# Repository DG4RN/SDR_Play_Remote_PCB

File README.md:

# SDR_Play_Remote_PCB
PCB design (by KiCad) for remote switched antenna input in connection with raspberry pi.

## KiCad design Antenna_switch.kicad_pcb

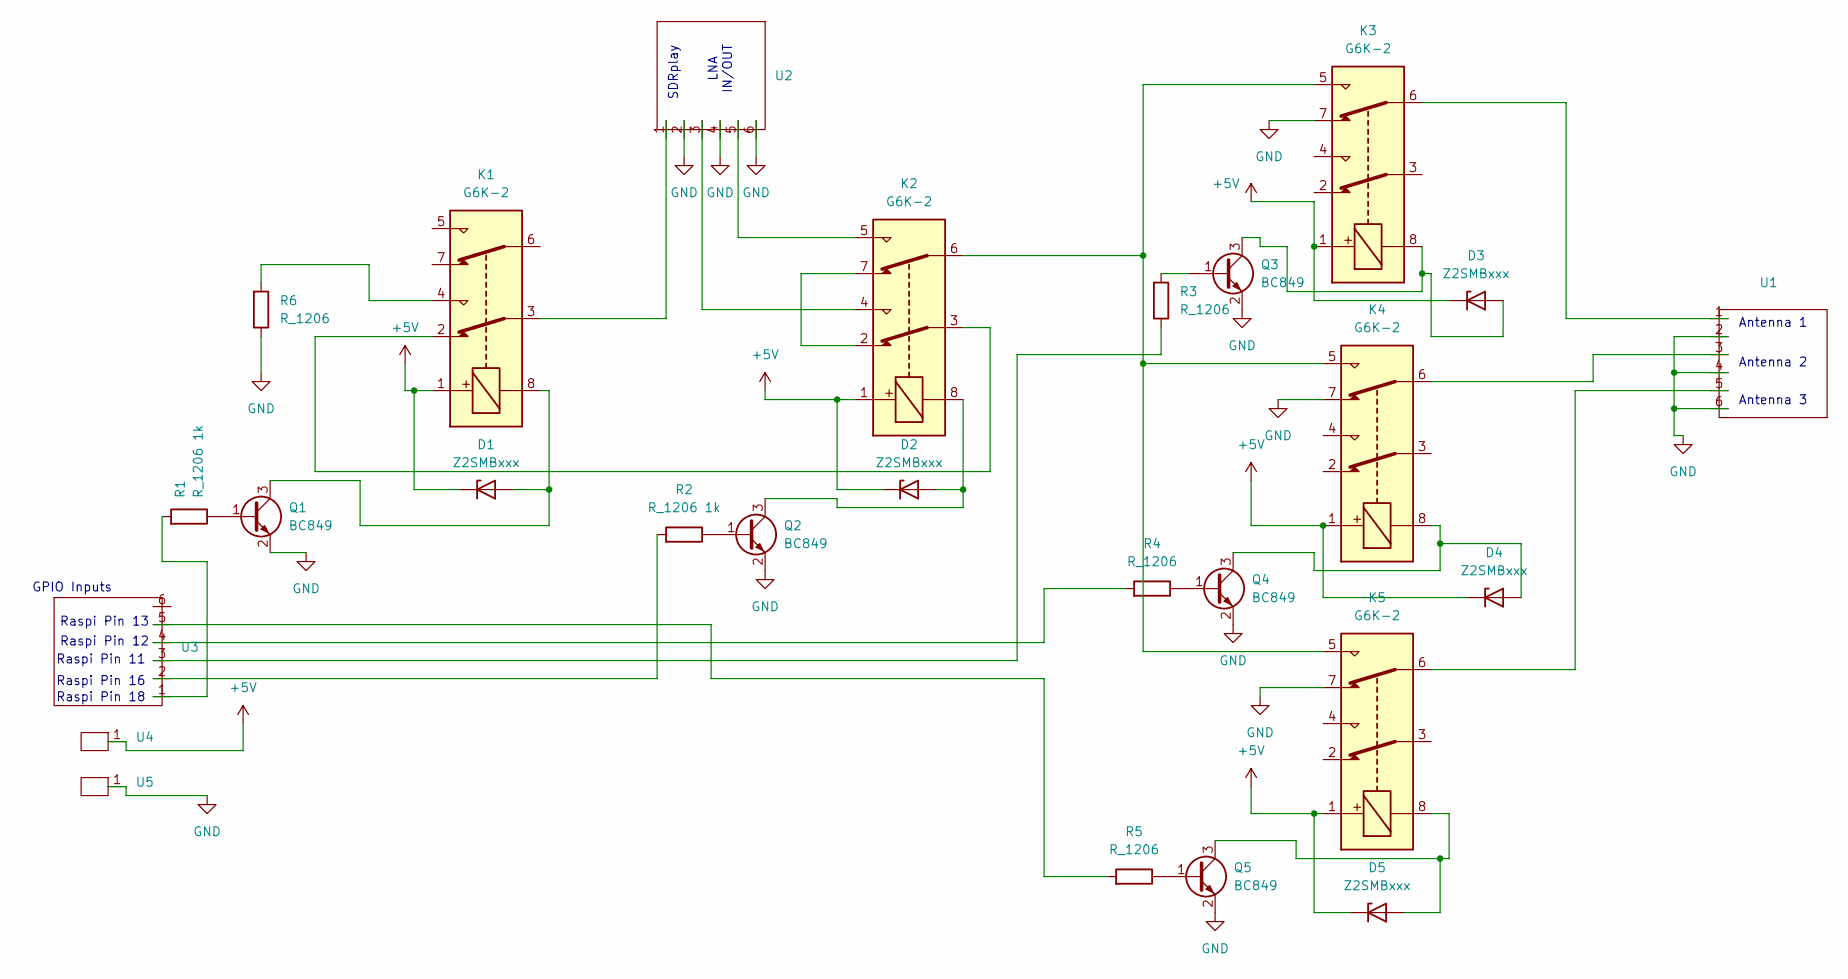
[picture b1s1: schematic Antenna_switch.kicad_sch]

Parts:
D1, D2, D3, D4, D5: Z2SMBxxx; D_SMB
K1, K2, K3, K4, K5: G6K-2; Relay_DPDT_Omron_G6K-2F-Y
Q1, Q2, Q3, Q4, Q5: BC849; SOT-23
R1, R2: R_1206 1k; R_1206_3216Metric
R3, R4, R5, R6: R_1206; R_1206_3216Metric
U1, U2, U3: Pad_IP-6
U4, U5: Lötpad_5_5

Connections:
+5V: D1.1 (K), D2.1 (K), D3.1 (K), D4.1 (K), D5.1 (K), K1.1, K2.1, K3.1, K4.1, K5.1, U4.1
GND: K3.7, K4.7, K5.7, Q1.2 (E), Q2.2 (E), Q3.2 (E), Q4.2 (E), Q5.2 (E), R6.2, U1.2, U1.4, U1.6, U2.2, U2.4, U2.6, U5.1
unnamed: D1.2 (A), K1.8, Q1.3 (C)
unnamed: D2.2 (A), K2.8, Q2.3 (C)
unnamed: D3.2 (A), K3.8, Q3.3 (C)
unnamed: D4.2 (A), K4.8, Q4.3 (C)
unnamed: D5.2 (A), K5.8, Q5.3 (C)
unnamed: K1.2, K2.3
unnamed: K1.3, U2.1
unnamed: K1.4, R6.1
unnamed: K2.2, K2.7
unnamed: K2.4, U2.3
unnamed: K2.5, U2.5
unnamed: K2.6, K3.5, K4.5, K5.5
unnamed: K3.6, U1.1
unnamed: K4.6, U1.3
unnamed: K5.6, U1.5
unnamed: Q1.1 (B), R1.2
unnamed: Q2.1 (B), R2.2
unnamed: Q3.1 (B), R3.1
unnamed: Q4.1 (B), R4.2
unnamed: Q5.1 (B), R5.2
unnamed: R1.1, U3.1
unnamed: R2.1, U3.2
unnamed: R3.2, U3.3
unnamed: R4.1, U3.4
unnamed: R5.1, U3.5

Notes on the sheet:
Raspi Pin 12
Antenna 3
Antenna 1
LNA IN/OUT
Raspi Pin 11
Raspi Pin 13
GPIO Inputs
Antenna 2
Raspi Pin 16
Raspi Pin 18
SDRplay

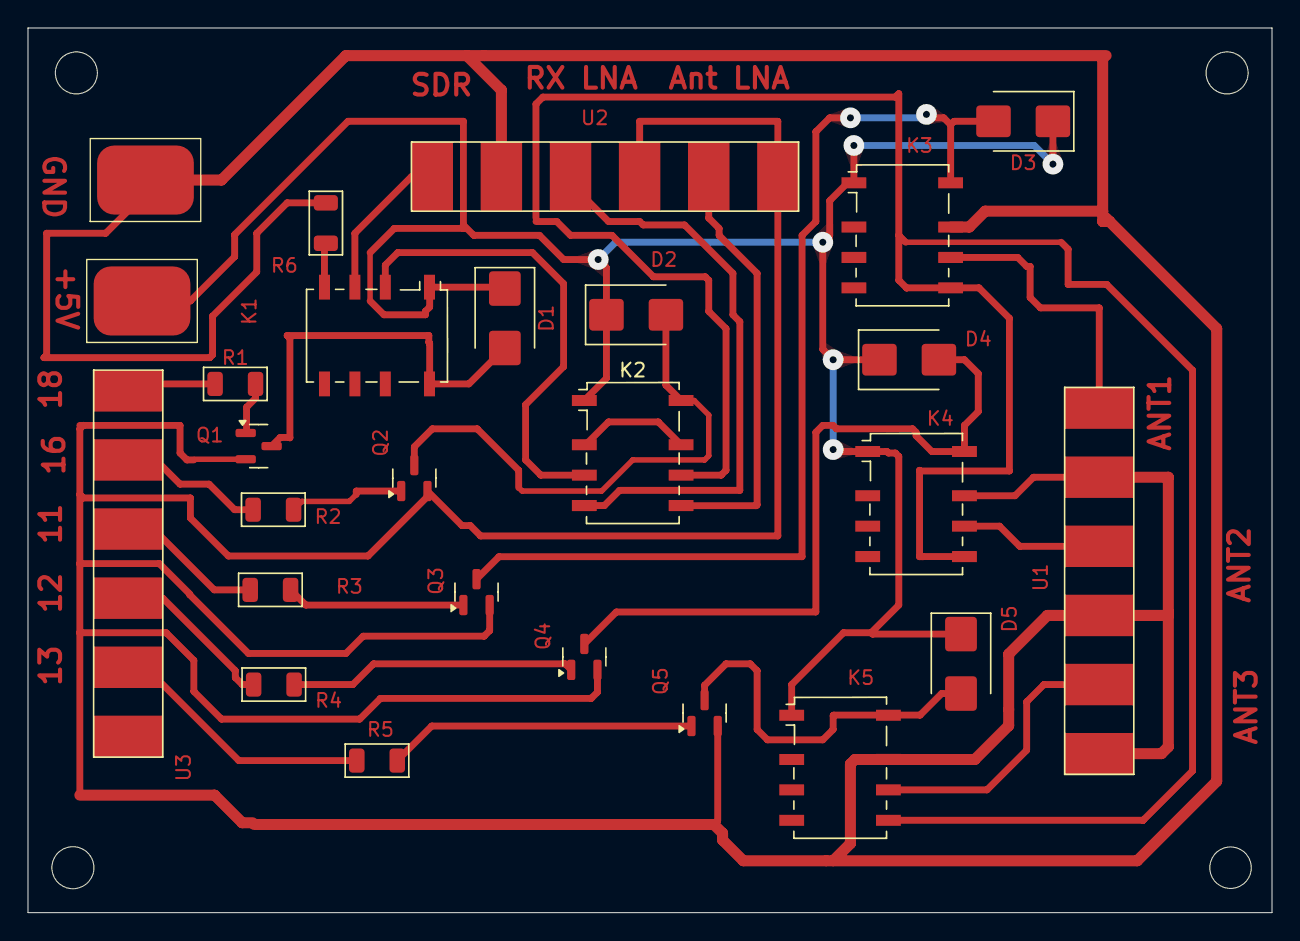
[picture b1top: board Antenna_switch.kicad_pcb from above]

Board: 2 copper layers, 90.0 x 64.0 mm, 26 parts (0 on the bottom side), 27 nets.
